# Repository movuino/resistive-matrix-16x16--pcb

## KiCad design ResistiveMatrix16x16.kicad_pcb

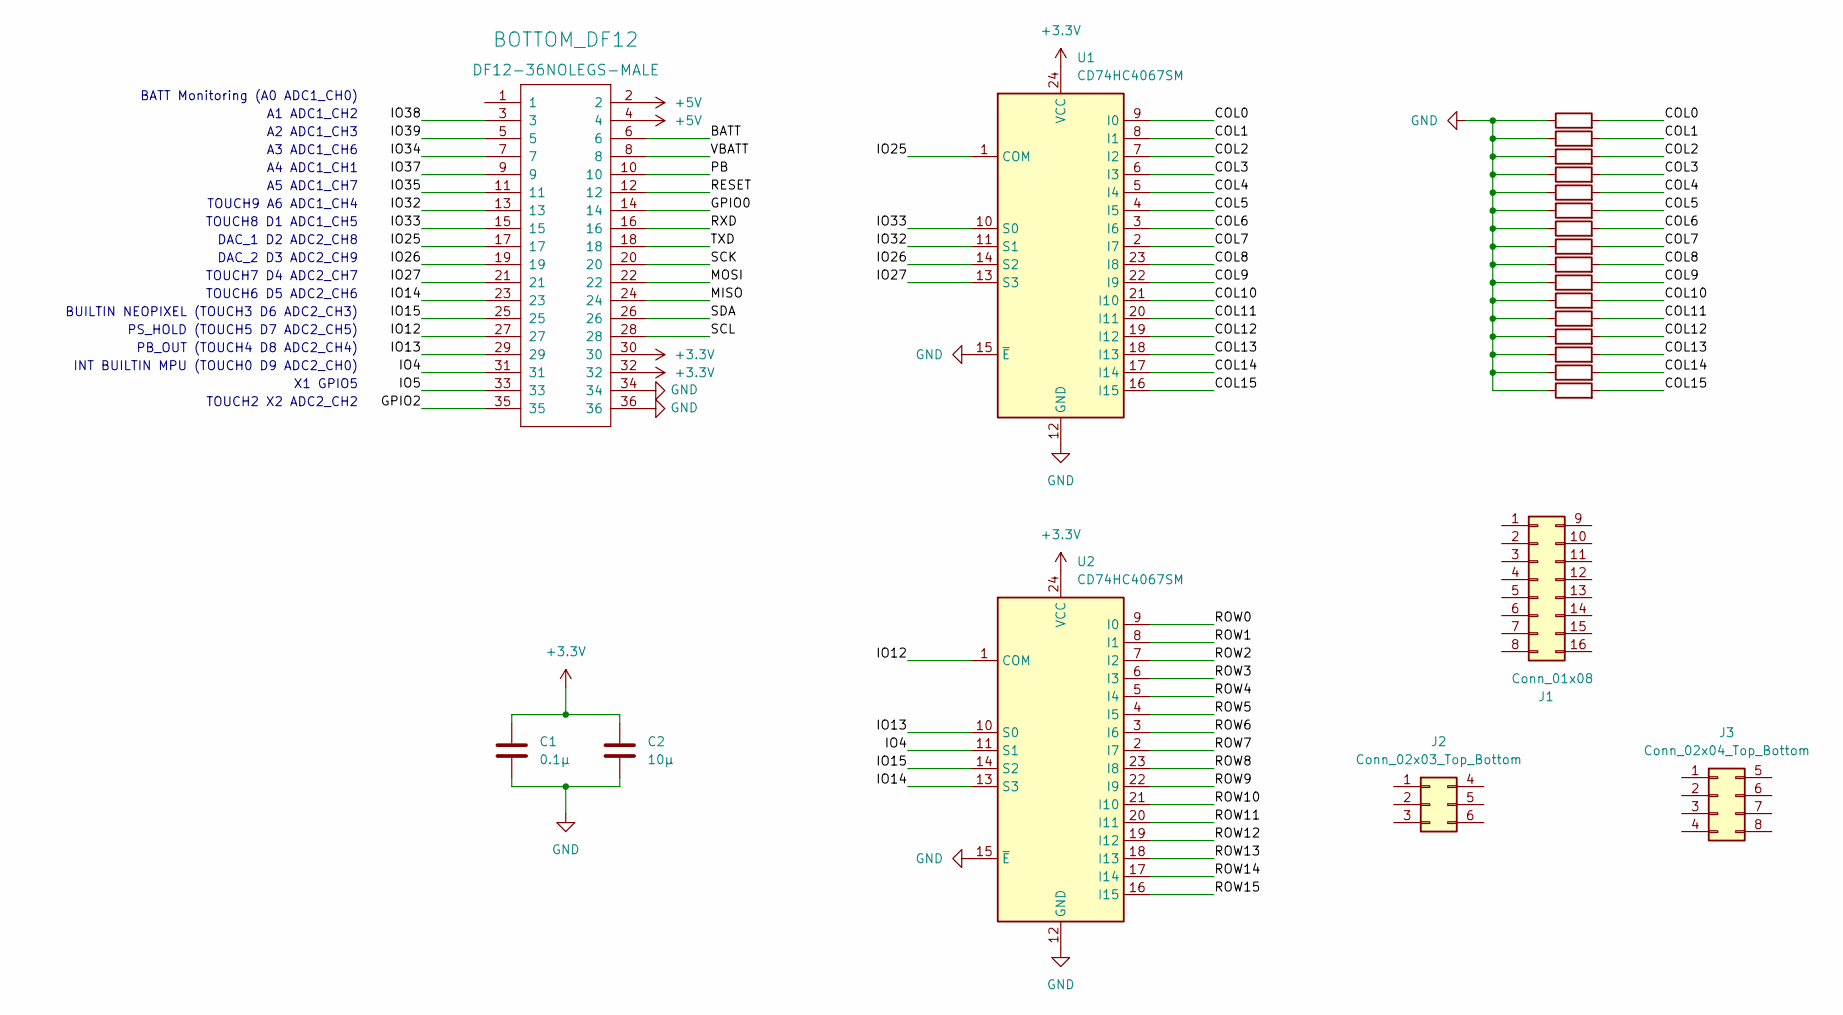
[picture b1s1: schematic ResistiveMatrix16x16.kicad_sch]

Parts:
BOTTOM_DF12: DF12-36NOLEGS-MALE; DF12-36-DP-NL
C1: 0.1µ; C_0603_1608Metric_Pad1.08x0.95mm_HandSolder
C2: 10µ; C_0603_1608Metric_Pad1.08x0.95mm_HandSolder
J1: Conn_01x08; PinHeader_2x08_P2.54mm_Vertical_SMD
J2: Conn_02x03_Top_Bottom; PinHeader_2x03_P2.54mm_Vertical_SMD
J3: Conn_02x04_Top_Bottom; PinHeader_2x04_P2.54mm_Vertical_SMD
R1, R2, R3, R4, R5, R6, R7, R8, R9, R10, R11, R12, R13, R14, R15, R16: R_Axial_DIN0207_L6.3mm_D2.5mm_P7.62mm_Horizontal
U1, U2: CD74HC4067SM; SSOP-24_5.3x8.2mm_P0.65mm

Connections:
+3.3V: BOTTOM_DF12.30, BOTTOM_DF12.32, C1.1, C2.1, U1.24 (VCC), U2.24 (VCC); also elsewhere on the board
+5V: BOTTOM_DF12.2, BOTTOM_DF12.4; also elsewhere on the board
/BATT: BOTTOM_DF12.6; also elsewhere on the board
/COL0: R1.2, U1.9 (I0)
/COL1: R2.2, U1.8 (I1)
/COL2: R3.2, U1.7 (I2)
/COL3: R4.2, U1.6 (I3)
/COL4: R5.2, U1.5 (I4)
/COL5: R6.2, U1.4 (I5)
/COL6: R7.2, U1.3 (I6)
/COL7: R8.2, U1.2 (I7)
/COL8: R9.2, U1.23 (I8)
/COL9: R10.2, U1.22 (I9)
/COL10: R11.2, U1.21 (I10)
/COL11: R12.2, U1.20 (I11)
/COL12: R13.2, U1.19 (I12)
/COL13: R14.2, U1.18 (I13)
/COL14: R15.2, U1.17 (I14)
/COL15: R16.2, U1.16 (I15)
/GPIO0: BOTTOM_DF12.14; also elsewhere on the board
/GPIO2: BOTTOM_DF12.35; also elsewhere on the board
/IO4: BOTTOM_DF12.31, U2.11 (S1); also elsewhere on the board
/IO5: BOTTOM_DF12.33; also elsewhere on the board
/IO12: BOTTOM_DF12.27, U2.1 (COM); also elsewhere on the board
/IO13: BOTTOM_DF12.29, U2.10 (S0); also elsewhere on the board
/IO14: BOTTOM_DF12.23, U2.13 (S3); also elsewhere on the board
/IO15: BOTTOM_DF12.25, U2.14 (S2); also elsewhere on the board
/IO25: BOTTOM_DF12.17, U1.1 (COM); also elsewhere on the board
/IO26: BOTTOM_DF12.19, U1.14 (S2); also elsewhere on the board
/IO27: BOTTOM_DF12.21, U1.13 (S3); also elsewhere on the board
/IO32: BOTTOM_DF12.13, U1.11 (S1); also elsewhere on the board
/IO33: BOTTOM_DF12.15, U1.10 (S0); also elsewhere on the board
/IO34: BOTTOM_DF12.7; also elsewhere on the board
/IO35: BOTTOM_DF12.11; also elsewhere on the board
/IO37: BOTTOM_DF12.9; also elsewhere on the board
/IO38: BOTTOM_DF12.3; also elsewhere on the board
/IO39: BOTTOM_DF12.5; also elsewhere on the board
/MISO: BOTTOM_DF12.24; also elsewhere on the board
/MOSI: BOTTOM_DF12.22; also elsewhere on the board
/PB: BOTTOM_DF12.10; also elsewhere on the board
/RESET: BOTTOM_DF12.12; also elsewhere on the board
/ROW0: U2.9 (I0)
/ROW1: U2.8 (I1)
/ROW2: U2.7 (I2)
/ROW3: U2.6 (I3)
/ROW4: U2.5 (I4)
/ROW5: U2.4 (I5)
/ROW6: U2.3 (I6)
/ROW7: U2.2 (I7)
/ROW8: U2.23 (I8)
/ROW9: U2.22 (I9)
/ROW10: U2.21 (I10)
/ROW11: U2.20 (I11)
/ROW12: U2.19 (I12)
/ROW13: U2.18 (I13)
/ROW14: U2.17 (I14)
/ROW15: U2.16 (I15)
/RXD: BOTTOM_DF12.16; also elsewhere on the board
/SCK: BOTTOM_DF12.20; also elsewhere on the board
/SCL: BOTTOM_DF12.28; also elsewhere on the board
/SDA: BOTTOM_DF12.26; also elsewhere on the board
/TXD: BOTTOM_DF12.18; also elsewhere on the board
/VBATT: BOTTOM_DF12.8; also elsewhere on the board
GND: BOTTOM_DF12.34, BOTTOM_DF12.36, C1.2, C2.2, R1.1, R2.1, R3.1, R4.1, R5.1, R6.1, R7.1, R8.1, R9.1, R10.1, R11.1, R12.1, R13.1, R14.1, R15.1, R16.1, U1.12 (GND), U1.15 (~E), U2.12 (GND), U2.15 (~E); also elsewhere on the board

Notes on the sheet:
TOUCH6 D5 ADC2_CH6
DAC_2 D3 ADC2_CH9
INT BUILTIN MPU (TOUCH0 D9 ADC2_CH0)
A2 ADC1_CH3
TOUCH9 A6 ADC1_CH4
A4 ADC1_CH1
A1 ADC1_CH2
A3 ADC1_CH6
TOUCH2 X2 ADC2_CH2
X1 GPIO5
TOUCH7 D4 ADC2_CH7
TOUCH8 D1 ADC1_CH5
A5 ADC1_CH7
PB_OUT (TOUCH4 D8 ADC2_CH4)
BATT Monitoring (A0 ADC1_CH0)
BUILTIN NEOPIXEL (TOUCH3 D6 ADC2_CH3)
DAC_1 D2 ADC2_CH8
PS_HOLD (TOUCH5 D7 ADC2_CH5)

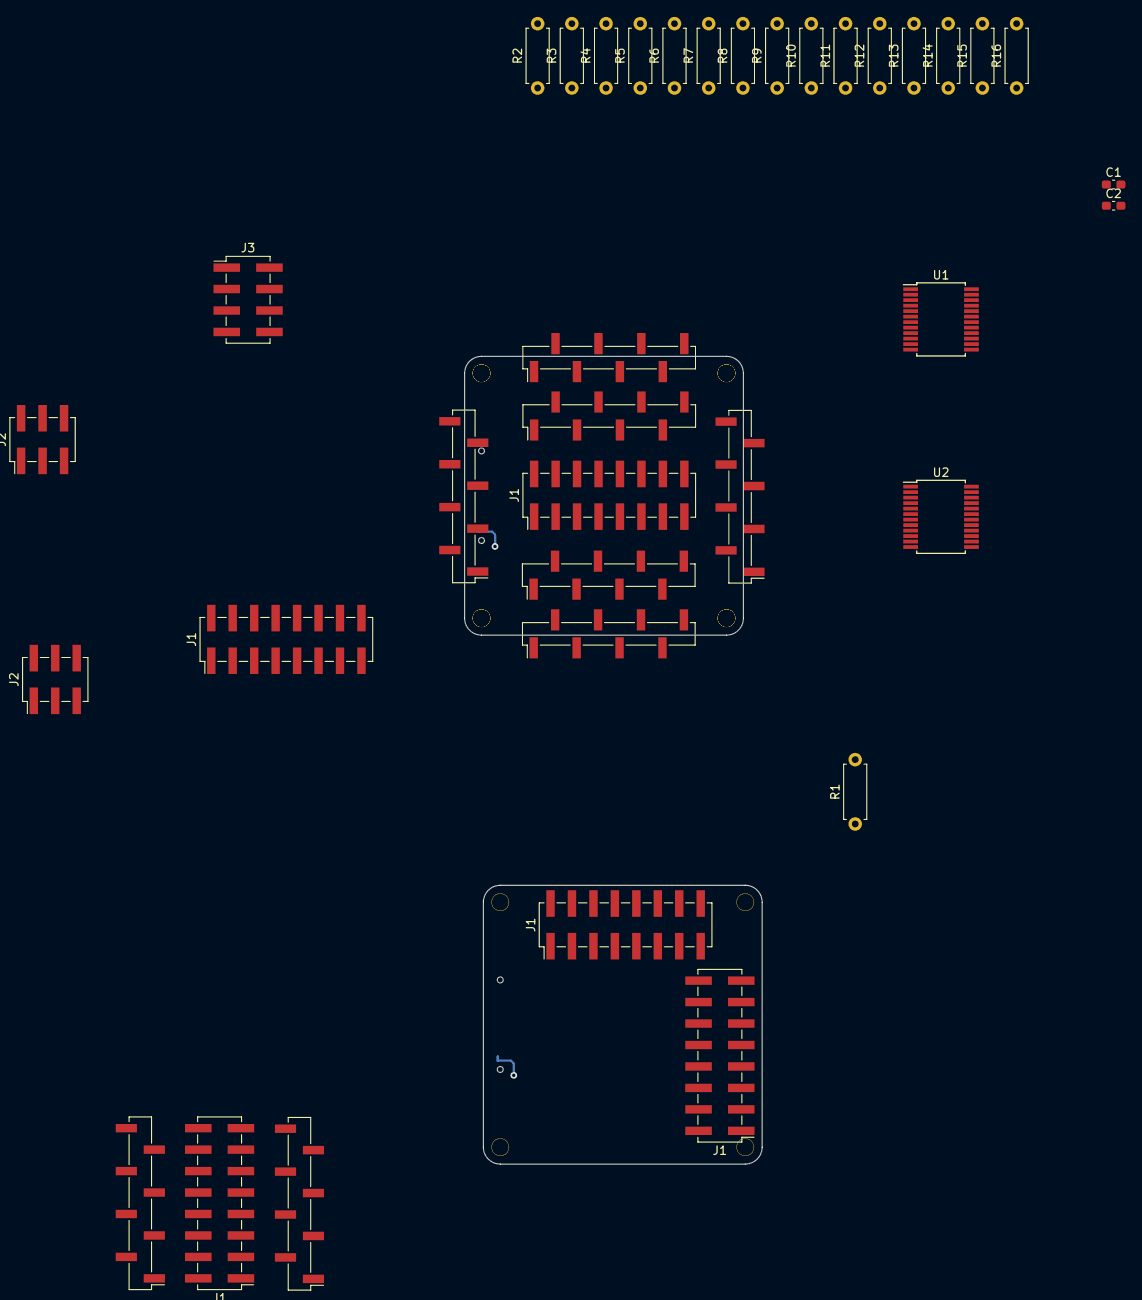
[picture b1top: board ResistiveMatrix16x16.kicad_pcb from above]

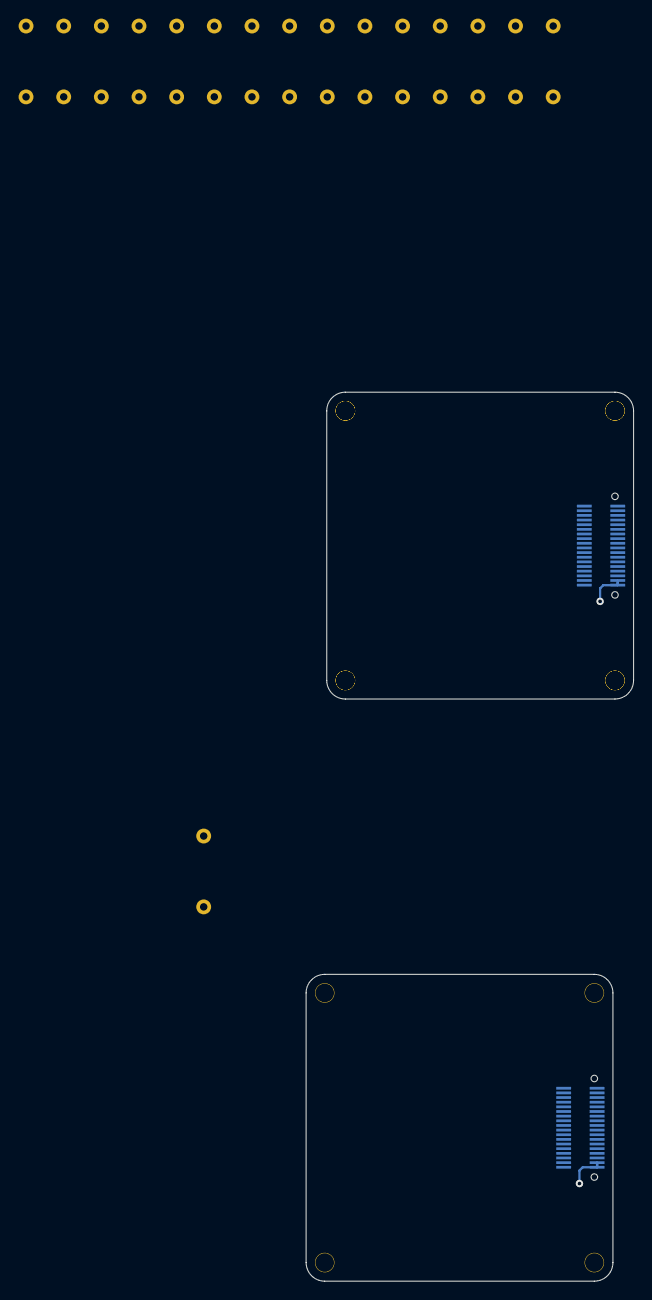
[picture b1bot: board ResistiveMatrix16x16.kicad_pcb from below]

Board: 2 copper layers, 30 parts (2 on the bottom side), 48 nets.

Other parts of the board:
BOTTOM_DF12#2: DF12-36NOLEGS-MALE; DF12-36-DP-NL
J1#2, J1#3, J1#4, J1#5: Conn_01x08; PinHeader_2x08_P2.54mm_Vertical_SMD
J2#2: Conn_02x03_Top_Bottom; PinHeader_2x03_P2.54mm_Vertical_SMD

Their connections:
+3.3V: BOTTOM_DF12#2.30, BOTTOM_DF12#2.32; also elsewhere on the board
+5V: BOTTOM_DF12#2.2, BOTTOM_DF12#2.4; also elsewhere on the board
/BATT: BOTTOM_DF12#2.6; also elsewhere on the board
/GPIO0: BOTTOM_DF12#2.14; also elsewhere on the board
/GPIO2: BOTTOM_DF12#2.35; also elsewhere on the board
/IO4: BOTTOM_DF12#2.31; also elsewhere on the board
/IO5: BOTTOM_DF12#2.33; also elsewhere on the board
/IO12: BOTTOM_DF12#2.27; also elsewhere on the board
/IO13: BOTTOM_DF12#2.29; also elsewhere on the board
/IO14: BOTTOM_DF12#2.23; also elsewhere on the board
/IO15: BOTTOM_DF12#2.25; also elsewhere on the board
/IO25: BOTTOM_DF12#2.17; also elsewhere on the board
/IO26: BOTTOM_DF12#2.19; also elsewhere on the board
/IO27: BOTTOM_DF12#2.21; also elsewhere on the board
/IO32: BOTTOM_DF12#2.13; also elsewhere on the board
/IO33: BOTTOM_DF12#2.15; also elsewhere on the board
/IO34: BOTTOM_DF12#2.7; also elsewhere on the board
/IO35: BOTTOM_DF12#2.11; also elsewhere on the board
/IO37: BOTTOM_DF12#2.9; also elsewhere on the board
/IO38: BOTTOM_DF12#2.3; also elsewhere on the board
/IO39: BOTTOM_DF12#2.5; also elsewhere on the board
/MISO: BOTTOM_DF12#2.24; also elsewhere on the board
/MOSI: BOTTOM_DF12#2.22; also elsewhere on the board
/PB: BOTTOM_DF12#2.10; also elsewhere on the board
/RESET: BOTTOM_DF12#2.12; also elsewhere on the board
/RXD: BOTTOM_DF12#2.16; also elsewhere on the board
/SCK: BOTTOM_DF12#2.20; also elsewhere on the board
/SCL: BOTTOM_DF12#2.28; also elsewhere on the board
/SDA: BOTTOM_DF12#2.26; also elsewhere on the board
/TXD: BOTTOM_DF12#2.18; also elsewhere on the board
/VBATT: BOTTOM_DF12#2.8; also elsewhere on the board
GND: BOTTOM_DF12#2.34, BOTTOM_DF12#2.36; also elsewhere on the board

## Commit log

2022-08-11 first
2022-08-11 python debug
2022-08-12 firmware
2022-08-12 update WifiOSC.h and _Complete firmware
2022-08-12 timerOSC0
2022-08-12 python bug fixed
2022-08-12 record.csv example
2023-11-05 init
